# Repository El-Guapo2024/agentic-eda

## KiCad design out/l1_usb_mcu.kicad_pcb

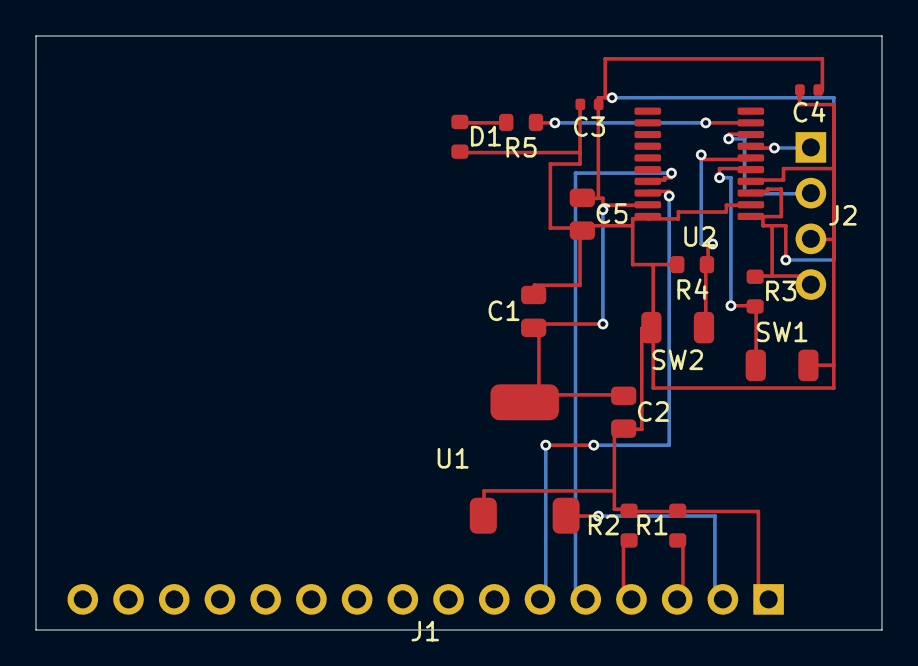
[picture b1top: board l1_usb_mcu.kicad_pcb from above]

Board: 2 copper layers, 47.0 x 33.0 mm, 17 parts (0 on the bottom side), 13 nets.

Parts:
C1: 10uF; 0805
C2: 22uF; 0805
C3, C4: 100nF; 0402
C5: 1uF; 0805
D1: status LED; 0603
J1: USB-C receptacle; PINHEADER-16
J2: SWD header; PINHEADER-4
R1, R2: 5.1k; 0603
R3, R4: 10k; 0603
R5: 330; 0603
SW1: reset button; 1206
SW2: boot0 button; 1206
U1: 3.3V LDO; SOT-223
U2: MCU; TSSOP-20

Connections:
3V3: C1.1, C2.1, C3.1, C4.1, C5.1, J2.4, R3.1, U1.2, U2.1, U2.3, U2.19
BOOT0: R4.1, SW2.1, U2.6
CC1: J1.3, R1.1
CC2: J1.4, R2.1
GND: C1.2, C2.2, C3.2, C4.2, C5.2, D1.2, J1.1, J2.3, R1.2, R2.2, R4.2, SW1.2, SW2.2, U1.1, U2.2, U2.4, U2.20
LED_A: D1.1, R5.2
LED_DRIVE: R5.1, U2.9
NRST: R3.2, SW1.1, U2.5
SWCLK: J2.2, U2.8
SWDIO: J2.1, U2.7
USB_DM: J1.6, U2.18
USB_DP: J1.5, U2.17
VBUS: J1.2, U1.3

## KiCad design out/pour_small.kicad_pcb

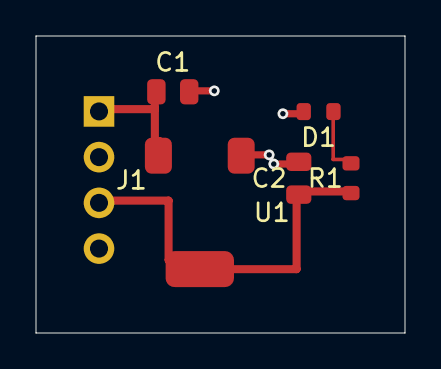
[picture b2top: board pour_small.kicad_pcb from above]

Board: 2 copper layers, 20.5 x 16.5 mm, 6 parts (0 on the bottom side), 4 nets.

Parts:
C1: 10uF; 0805
C2: 22uF; 0805
D1: PWR; 0603
J1: HDR; PINHEADER-4
R1: 1k; 0603
U1: 3.3V LDO; SOT-223

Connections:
GND: C1.2, C2.2, D1.2, J1.2, U1.1
LED_A: D1.1, R1.2
VIN: C1.1, J1.1, U1.3
VOUT: C2.1, J1.3, R1.1, U1.2

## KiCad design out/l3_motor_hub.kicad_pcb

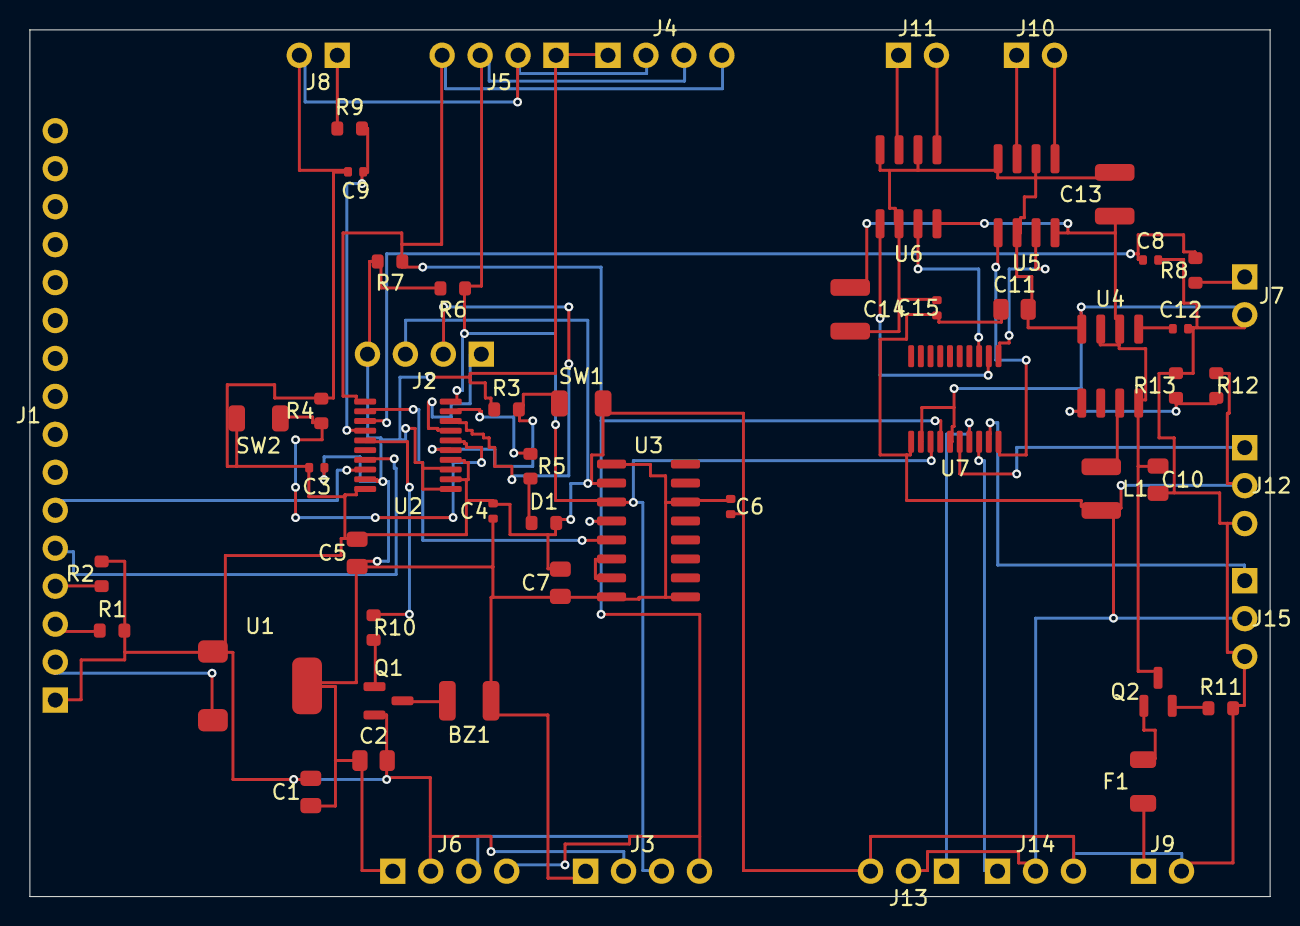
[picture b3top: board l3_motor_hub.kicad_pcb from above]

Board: 2 copper layers, 83.0 x 58.0 mm, 58 parts (0 on the bottom side), 44 nets.

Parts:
BZ1: magnetic buzzer; 1210
C1, C10: 10uF; 0805
C2, C11: 22uF; 0805
C3, C4, C6, C8, C9, C12, C15: 100nF; 0402
C5, C7: 1uF; 0805
C13, C14: 100uF bulk; 1210
D1: status LED; 0603
F1: 1A polyfuse; 1206
J1: USB-C receptacle; PINHEADER-16
J2: SWD header; PINHEADER-4
J3, J4, J5, J6: I2C sensor header; PINHEADER-4
J7: analog input 1; PINHEADER-2
J8: analog input 2; PINHEADER-2
J9: battery input (2S LiPo); PINHEADER-2
J10: motor 1 output; PINHEADER-2
J11: motor 2 output; PINHEADER-2
J12: servo header 1; PINHEADER-3
J13: servo header 2; PINHEADER-3
J14: servo header 3; PINHEADER-3
J15: servo header 4; PINHEADER-3
L1: 4.7uH power inductor; 1210
Q1: NPN switch; SOT-23
Q2: P-FET reverse-polarity; SOT-23
R1, R2: 5.1k; 0603
R3, R4, R11, R12: 10k; 0603
R5: 330; 0603
R6, R7: 4.7k; 0603
R8, R9, R10: 1k; 0603
R13: 3.3k; 0603
SW1: reset button; 1206
SW2: boot0 button; 1206
U1: 3.3V LDO; SOT-223
U2: MCU; TSSOP-20
U3: 6-axis IMU; SOIC-16
U4: 5V buck converter; SOIC-8
U5: H-bridge motor driver 1; SOIC-8
U6: H-bridge motor driver 2; SOIC-8
U7: 16-ch I2C PWM driver; TSSOP-20

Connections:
3V3: BZ1.1, C1.1, C2.1, C3.1, C4.1, C5.1, C6.1, C7.1, J2.4, J3.1, J4.1, J5.1, J6.1, R3.1, R6.2, R7.2, U1.2, U2.1, U2.3, U2.19, U3.1, U3.8, U3.9, U3.14
5V: C11.1, C15.1, J12.2, J13.2, J14.2, J15.2, L1.2, R12.1, U7.1
AIN1_FILT: C8.1, R8.2, U2.13
AIN1_RAW: J7.1, R8.1
AIN2_FILT: C9.1, R9.2, U2.14
AIN2_RAW: J8.1, R9.1
BOOT0: R4.1, SW2.1, U2.6
BUCK_BOOT: C12.1, U4.1
BUCK_FB: R12.2, R13.1, U4.5
BUCK_SW: L1.1, U4.7
BUZZ_BASE: R10.1, U2.15
BUZZ_DRIVE: BZ1.2, Q1.3
BUZZ_SW: Q1.1, R10.2
CC1: J1.3, R1.1
CC2: J1.4, R2.1
GATE_PULL: Q2.2, R11.1
GND: C1.2, C2.2, C3.2, C4.2, C5.2, C6.2, C7.2, C8.2, C9.2, C10.2, C11.2, C12.2, C13.2, C14.2, C15.2, D1.2, J1.1, J2.3, J3.2, J4.2, J5.2, J6.2, J7.2, J8.2, J9.2, J12.3, J13.3, J14.3, J15.3, Q1.2, R1.2, R2.2, R4.2, R11.2, R13.2, SW1.2, SW2.2, U1.1, U2.2, U2.4, U2.20, U3.2, U4.4, U5.2, U5.6, U5.8, U6.2, U6.6, U6.8, U7.2, U7.5
I2C_SCL: J3.3, J4.3, J5.3, J6.3, R6.1, U2.10, U3.3, U7.3
I2C_SDA: J3.4, J4.4, J5.4, J6.4, R7.1, U2.11, U3.4, U7.4
IMU_AD0: U3.6, U3.7
IMU_INT: U2.12, U3.5
LED_A: D1.1, R5.2
LED_DRIVE: R5.1, U2.9
M1_IN1: U5.1, U7.10
M1_IN2: U5.3, U7.11
M1_OUT1: J10.1, U5.7
M1_OUT2: J10.2, U5.5
M2_IN1: U6.1, U7.12
M2_IN2: U6.3, U7.13
M2_OUT1: J11.1, U6.7
M2_OUT2: J11.2, U6.5
NRST: R3.2, SW1.1, U2.5
SERVO1: J12.1, U7.6
SERVO2: J13.1, U7.7
SERVO3: J14.1, U7.8
SERVO4: J15.1, U7.9
SWCLK: J2.2, U2.8
SWDIO: J2.1, U2.7
USB_DM: J1.6, U2.18
USB_DP: J1.5, U2.17
VBAT: C10.1, C13.1, C14.1, Q2.3, U4.2, U4.3, U4.8, U5.4, U6.4
VBAT_FUSED: F1.2, Q2.1
VBAT_RAW: F1.1, J9.1
VBUS: J1.2, U1.3
